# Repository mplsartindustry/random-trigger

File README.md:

# random-trigger

Eurorack trigger randomizer and white noise generator

#### Front View:

#### Back View:

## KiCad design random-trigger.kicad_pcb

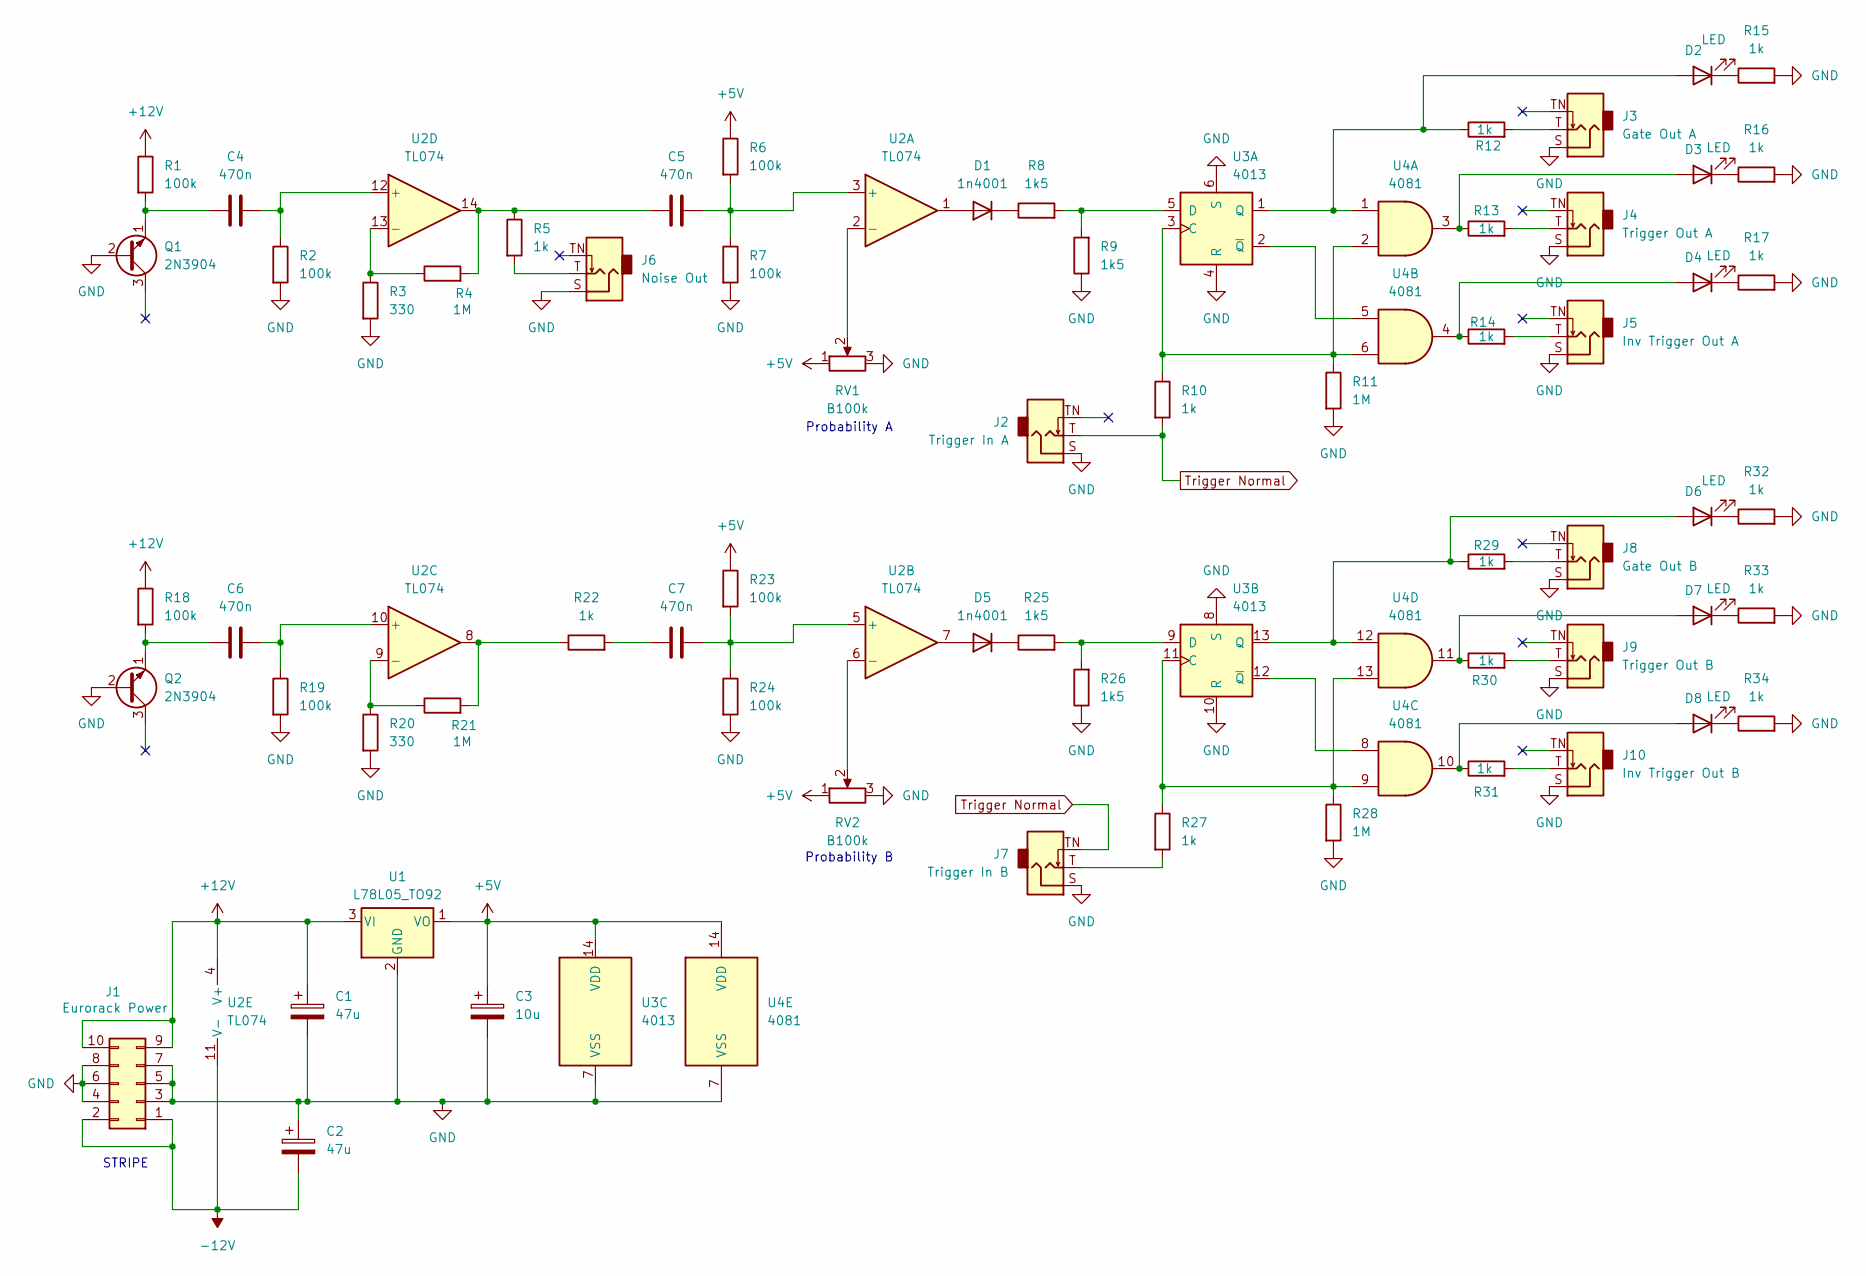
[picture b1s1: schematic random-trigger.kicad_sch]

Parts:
C1, C2: 47u; CP_Radial_D5.0mm_P2.50mm
C3: 10u; CP_Radial_D5.0mm_P2.50mm
C4, C5, C6, C7: 470n; C_Rect_L7.2mm_W3.5mm_P5.00mm_FKS2_FKP2_MKS2_MKP2
D1, D5: 1n4001; D_A-405_P7.62mm_Horizontal
D2, D3, D4, D6, D7, D8: LED; LED_D3.0mm
J1: Eurorack Power; IDC-Header_2x05_P2.54mm_Vertical
J2: Trigger In A; Jack_3.5mm_QingPu_WQP-PJ301BM_Vertical
J3: Gate Out A; Jack_3.5mm_QingPu_WQP-PJ301BM_Vertical
J4: Trigger Out A; Jack_3.5mm_QingPu_WQP-PJ301BM_Vertical
J5: Inv Trigger Out A; Jack_3.5mm_QingPu_WQP-PJ301BM_Vertical
J6: Noise Out; Jack_3.5mm_QingPu_WQP-PJ301BM_Vertical
J7: Trigger In B; Jack_3.5mm_QingPu_WQP-PJ301BM_Vertical
J8: Gate Out B; Jack_3.5mm_QingPu_WQP-PJ301BM_Vertical
J9: Trigger Out B; Jack_3.5mm_QingPu_WQP-PJ301BM_Vertical
J10: Inv Trigger Out B; Jack_3.5mm_QingPu_WQP-PJ301BM_Vertical
Q1, Q2: 2N3904; TO-92_Inline
R1, R2, R6, R7, R18, R19, R23, R24: 100k; R_Axial_DIN0207_L6.3mm_D2.5mm_P7.62mm_Horizontal
R3, R20: 330; R_Axial_DIN0207_L6.3mm_D2.5mm_P7.62mm_Horizontal
R4, R11, R21, R28: 1M; R_Axial_DIN0207_L6.3mm_D2.5mm_P7.62mm_Horizontal
R5, R10, R12, R13, R14, R15, R16, R17, R22, R27, R29, R30, R31, R32, R33, R34: 1k; R_Axial_DIN0207_L6.3mm_D2.5mm_P7.62mm_Horizontal
R8, R9, R25, R26: 1k5; R_Axial_DIN0207_L6.3mm_D2.5mm_P7.62mm_Horizontal
RV1, RV2: B100k; Potentiometer_Alpha_RD901F-40-00D_Single_Vertical
U1: L78L05_TO92; TO-92_Inline
U2: TL074; DIP-14_W7.62mm_Socket_WithChip
U3: 4013; DIP-14_W7.62mm_Socket_WithChip
U4: 4081; DIP-14_W7.62mm_Socket_WithChip

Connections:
+5V: C3.1, R6.1, R23.1, RV1.1, RV2.1, U1.1 (VO), U3.14 (VDD), U4.14 (VDD)
+12V: C1.1, J1.9, J1.10, R1.1, R18.1, U1.3 (VI), U2.4 (V+)
-12V: C2.2, J1.1, J1.2, U2.11 (V-)
GND: C1.2, C2.1, C3.2, J1.3, J1.4, J1.5, J1.6, J1.7, J1.8, J2.S, J3.S, J4.S, J5.S, J6.S, J7.S, J8.S, J9.S, J10.S, Q1.2 (B), Q2.2 (B), R2.2, R3.2, R7.2, R9.1, R11.2, R15.2, R16.2, R17.2, R19.2, R20.2, R24.2, R26.1, R28.2, R32.2, R33.2, R34.2, RV1.3, RV2.3, U1.2 (GND), U3.4 (R), U3.6 (S), U3.7 (VSS), U3.8 (S), U3.10 (R), U4.7 (VSS)
unnamed: C5.1, R4.2, R5.1, U2.14
unnamed: C7.1, R22.2
unnamed: D1.2 (A), U2.1
unnamed: D1.1 (K), R8.1
unnamed: D2.2 (A), R12.1, U3.1 (Q), U4.1
unnamed: D2.1 (K), R15.1
unnamed: D3.2 (A), R13.1, U4.3
unnamed: D3.1 (K), R16.1
unnamed: D4.2 (A), R14.1, U4.4
unnamed: D4.1 (K), R17.1
unnamed: D5.2 (A), U2.7
unnamed: D5.1 (K), R25.1
unnamed: D6.2 (A), R29.1, U3.13 (Q), U4.12
unnamed: D6.1 (K), R32.1
unnamed: D7.2 (A), R30.1, U4.11
unnamed: D7.1 (K), R33.1
unnamed: D8.2 (A), R31.1, U4.10
unnamed: D8.1 (K), R34.1
unnamed: J3.T, R12.2
unnamed: J4.T, R13.2
unnamed: J5.T, R14.2
unnamed: J6.T, R5.2
unnamed: J7.T, R27.2
unnamed: J8.T, R29.2
unnamed: J9.T, R30.2
unnamed: J10.T, R31.2
unnamed: C4.1, Q1.1 (E), R1.2
unnamed: C6.1, Q2.1 (E), R18.2
unnamed: R21.2, R22.1, U2.8
unnamed: C5.2, R6.2, R7.1, U2.3 (+)
unnamed: RV1.2, U2.2 (-)
unnamed: C7.2, R23.2, R24.1, U2.5 (+)
unnamed: RV2.2, U2.6 (-)
unnamed: C6.2, R19.1, U2.10 (+)
unnamed: R20.1, R21.1, U2.9 (-)
unnamed: C4.2, R2.1, U2.12 (+)
unnamed: R3.1, R4.1, U2.13 (-)
unnamed: R10.1, R11.1, U3.3 (C), U4.2, U4.6
unnamed: R8.2, R9.2, U3.5 (D)
unnamed: U3.2 (~Q), U4.5
unnamed: R27.1, R28.1, U3.11 (C), U4.9, U4.13
unnamed: R25.2, R26.2, U3.9 (D)
unnamed: U3.12 (~Q), U4.8
Trigger Normal: J2.T, J7.TN, R10.2

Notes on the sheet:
Probability B
STRIPE
Probability A

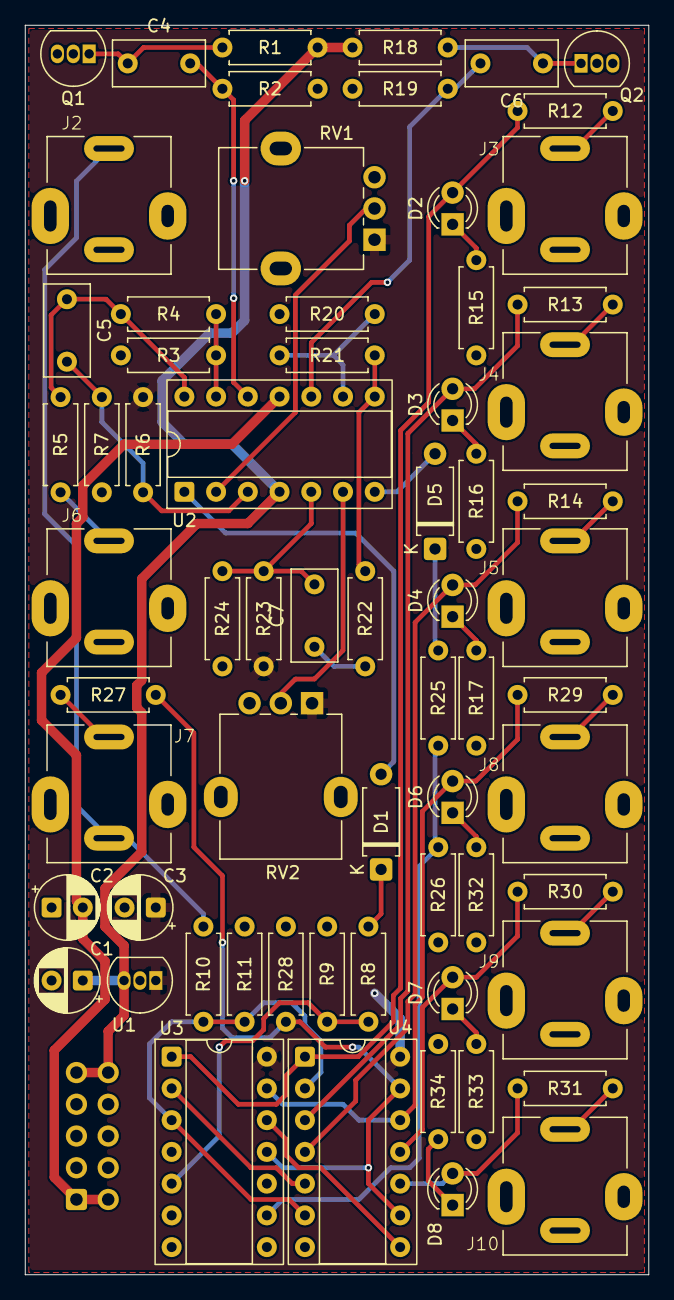
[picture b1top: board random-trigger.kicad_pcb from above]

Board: 2 copper layers, 49.9 x 100.0 mm, 67 parts (1 on the bottom side), 48 nets.

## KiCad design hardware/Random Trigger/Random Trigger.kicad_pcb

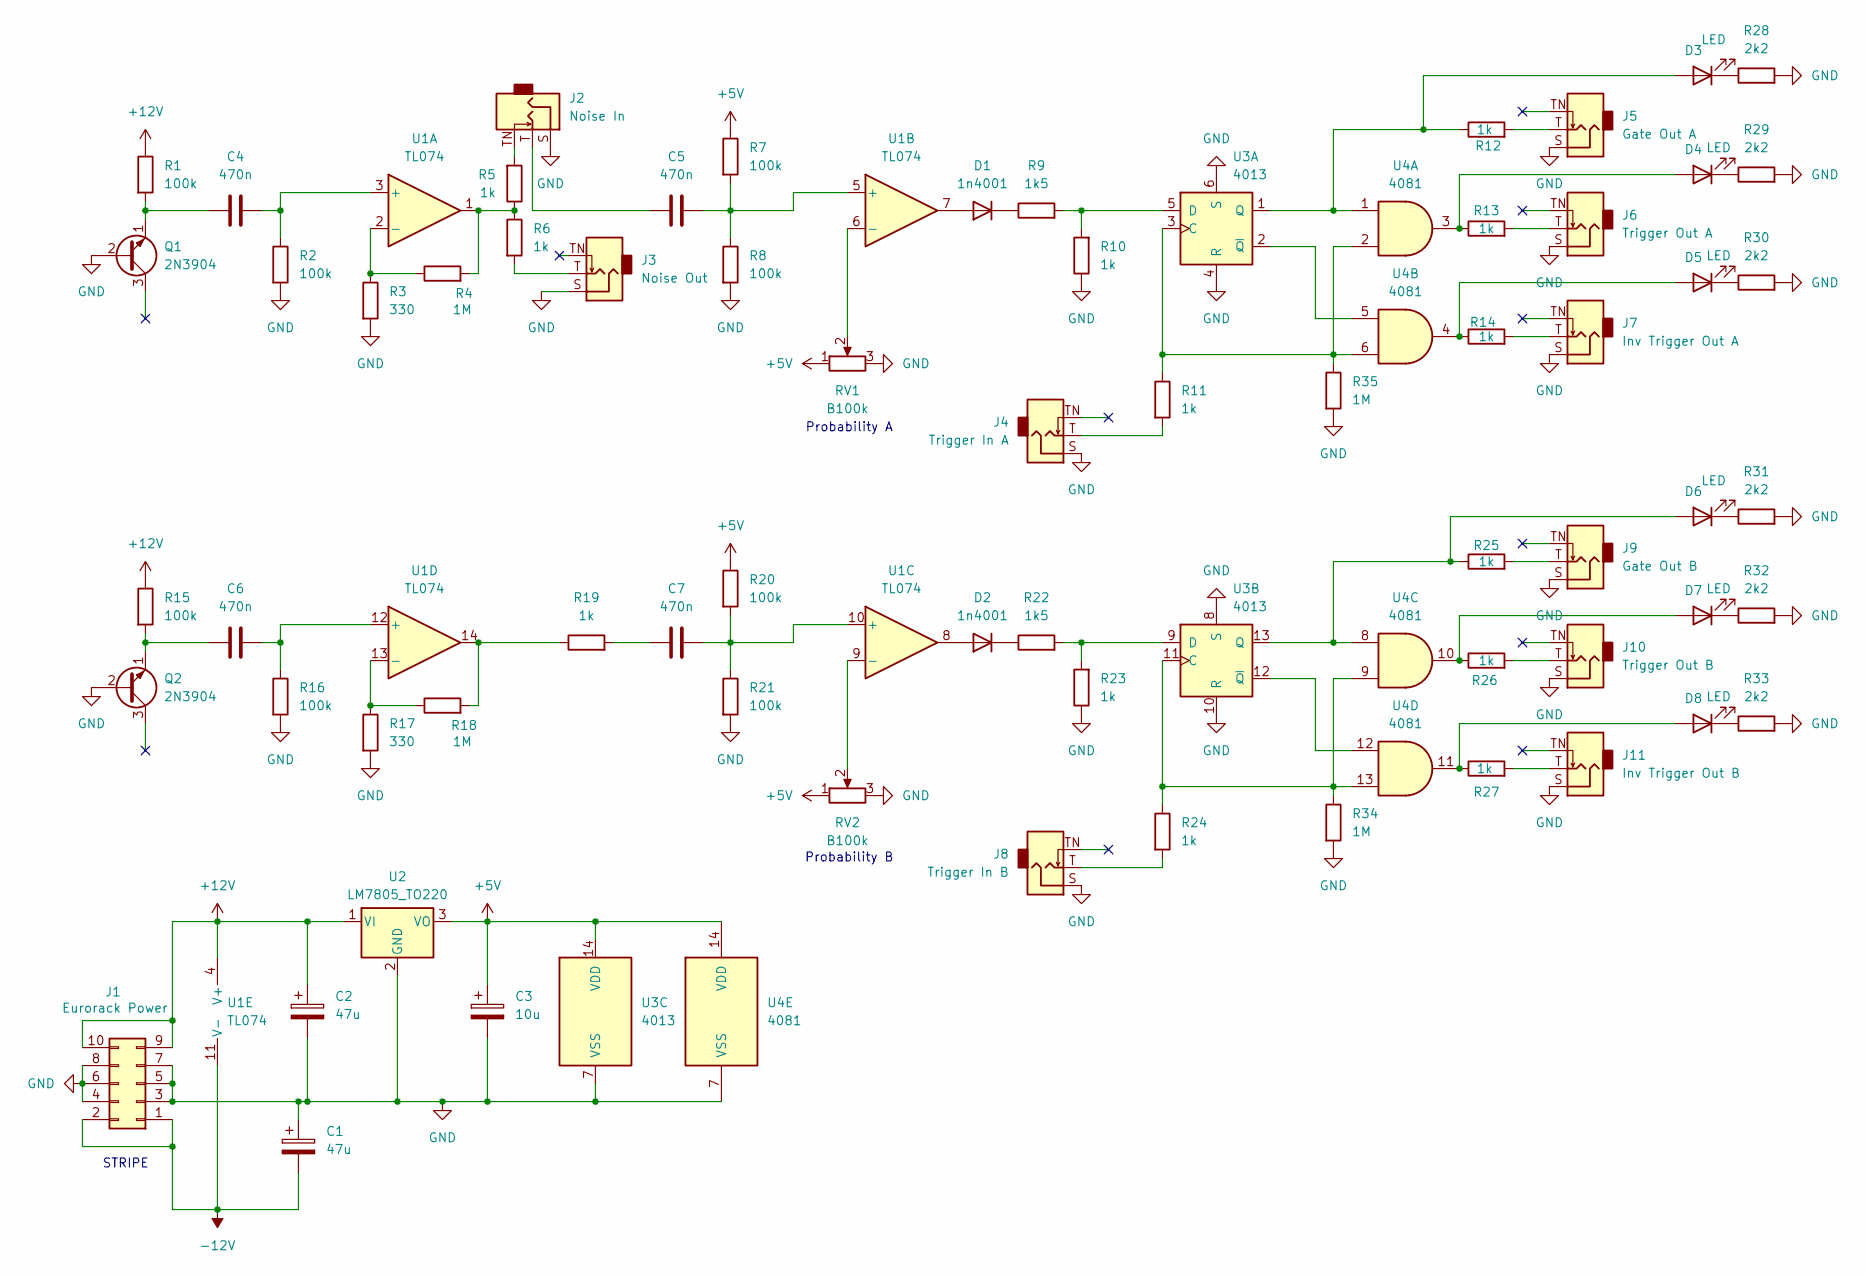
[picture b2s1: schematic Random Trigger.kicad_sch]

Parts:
C1, C2: 47u; CP_Radial_D6.3mm_P2.50mm
C3: 10u; CP_Radial_D5.0mm_P2.50mm
C4, C5, C6, C7: 470n; C_Rect_L7.0mm_W3.5mm_P5.00mm
D1, D2: 1n4001; D_A-405_P7.62mm_Horizontal
D3, D4, D5, D6, D7, D8: LED; LED_D3.0mm
J1: Eurorack Power; IDC-Header_2x05_P2.54mm_Vertical
J2: Noise In; Jack_3.5mm_QingPu_WQP-PJ301BM_Vertical
J3: Noise Out; Jack_3.5mm_QingPu_WQP-PJ301BM_Vertical
J4: Trigger In A; Jack_3.5mm_QingPu_WQP-PJ301BM_Vertical
J5: Gate Out A; Jack_3.5mm_QingPu_WQP-PJ301BM_Vertical
J6: Trigger Out A; Jack_3.5mm_QingPu_WQP-PJ301BM_Vertical
J7: Inv Trigger Out A; Jack_3.5mm_QingPu_WQP-PJ301BM_Vertical
J8: Trigger In B; Jack_3.5mm_QingPu_WQP-PJ301BM_Vertical
J9: Gate Out B; Jack_3.5mm_QingPu_WQP-PJ301BM_Vertical
J10: Trigger Out B; Jack_3.5mm_QingPu_WQP-PJ301BM_Vertical
J11: Inv Trigger Out B; Jack_3.5mm_QingPu_WQP-PJ301BM_Vertical
Q1, Q2: 2N3904; TO-92_Inline
R1, R2, R7, R8, R15, R16, R20, R21: 100k; R_Axial_DIN0207_L6.3mm_D2.5mm_P7.62mm_Horizontal
R3, R17: 330; R_Axial_DIN0207_L6.3mm_D2.5mm_P7.62mm_Horizontal
R4, R18, R34, R35: 1M; R_Axial_DIN0207_L6.3mm_D2.5mm_P7.62mm_Horizontal
R5, R6, R10, R11, R12, R13, R14, R19, R23, R24, R25, R26, R27: 1k; R_Axial_DIN0207_L6.3mm_D2.5mm_P7.62mm_Horizontal
R9, R22: 1k5; R_Axial_DIN0207_L6.3mm_D2.5mm_P7.62mm_Horizontal
R28, R29, R30, R31, R32, R33: 2k2; R_Axial_DIN0207_L6.3mm_D2.5mm_P7.62mm_Horizontal
RV1, RV2: B100k; Potentiometer_Alpha_RD901F-40-00D_Single_Vertical
U1: TL074; DIP-14_W7.62mm_Socket
U2: LM7805_TO220; TO-220-3_Vertical
U3: 4013; DIP-14_W7.62mm_Socket
U4: 4081; DIP-14_W7.62mm_Socket

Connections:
+5V: C3.1, R7.1, R20.1, RV1.1, RV2.1, U2.3 (VO), U3.14 (VDD), U4.14 (VDD)
+12V: C2.1, J1.9, J1.10, R1.1, R15.1, U1.4 (V+), U2.1 (VI)
-12V: C1.2, J1.1, J1.2, U1.11 (V-)
GND: C1.1, C2.2, C3.2, J1.3, J1.4, J1.5, J1.6, J1.7, J1.8, J2.S, J3.S, J4.S, J5.S, J6.S, J7.S, J8.S, J9.S, J10.S, J11.S, Q1.2 (B), Q2.2 (B), R2.2, R3.2, R8.2, R10.1, R16.2, R17.2, R21.2, R23.1, R28.2, R29.2, R30.2, R31.2, R32.2, R33.2, R34.2, R35.2, RV1.3, RV2.3, U2.2 (GND), U3.4 (R), U3.6 (S), U3.7 (VSS), U3.8 (S), U3.10 (R), U4.7 (VSS)
unnamed: C5.1, J2.T
unnamed: C7.1, R19.2
unnamed: D1.2 (A), U1.7
unnamed: D1.1 (K), R9.1
unnamed: D2.2 (A), U1.8
unnamed: D2.1 (K), R22.1
unnamed: D3.2 (A), R12.1, U3.1 (Q), U4.1
unnamed: D3.1 (K), R28.1
unnamed: D4.2 (A), R13.1, U4.3
unnamed: D4.1 (K), R29.1
unnamed: D5.2 (A), R14.1, U4.4
unnamed: D5.1 (K), R30.1
unnamed: D6.2 (A), R25.1, U3.13 (Q), U4.8
unnamed: D6.1 (K), R31.1
unnamed: D7.2 (A), R26.1, U4.10
unnamed: D7.1 (K), R32.1
unnamed: D8.2 (A), R27.1, U4.11
unnamed: D8.1 (K), R33.1
unnamed: J2.TN, R5.2
unnamed: J3.T, R6.2
unnamed: J4.T, R11.2
unnamed: J5.T, R12.2
unnamed: J6.T, R13.2
unnamed: J7.T, R14.2
unnamed: J8.T, R24.2
unnamed: J9.T, R25.2
unnamed: J10.T, R26.2
unnamed: J11.T, R27.2
unnamed: C4.1, Q1.1 (E), R1.2
unnamed: C6.1, Q2.1 (E), R15.2
unnamed: R4.2, R5.1, R6.1, U1.1
unnamed: R18.2, R19.1, U1.14
unnamed: C4.2, R2.1, U1.3 (+)
unnamed: R3.1, R4.1, U1.2 (-)
unnamed: C5.2, R7.2, R8.1, U1.5 (+)
unnamed: RV1.2, U1.6 (-)
unnamed: C7.2, R20.2, R21.1, U1.10 (+)
unnamed: RV2.2, U1.9 (-)
unnamed: C6.2, R16.1, U1.12 (+)
unnamed: R17.1, R18.1, U1.13 (-)
unnamed: R11.1, R35.1, U3.3 (C), U4.2, U4.6
unnamed: R9.2, R10.2, U3.5 (D)
unnamed: U3.2 (~Q), U4.5
unnamed: R24.1, R34.1, U3.11 (C), U4.9, U4.13
unnamed: R22.2, R23.2, U3.9 (D)
unnamed: U3.12 (~Q), U4.12

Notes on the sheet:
Probability B
STRIPE
Probability A

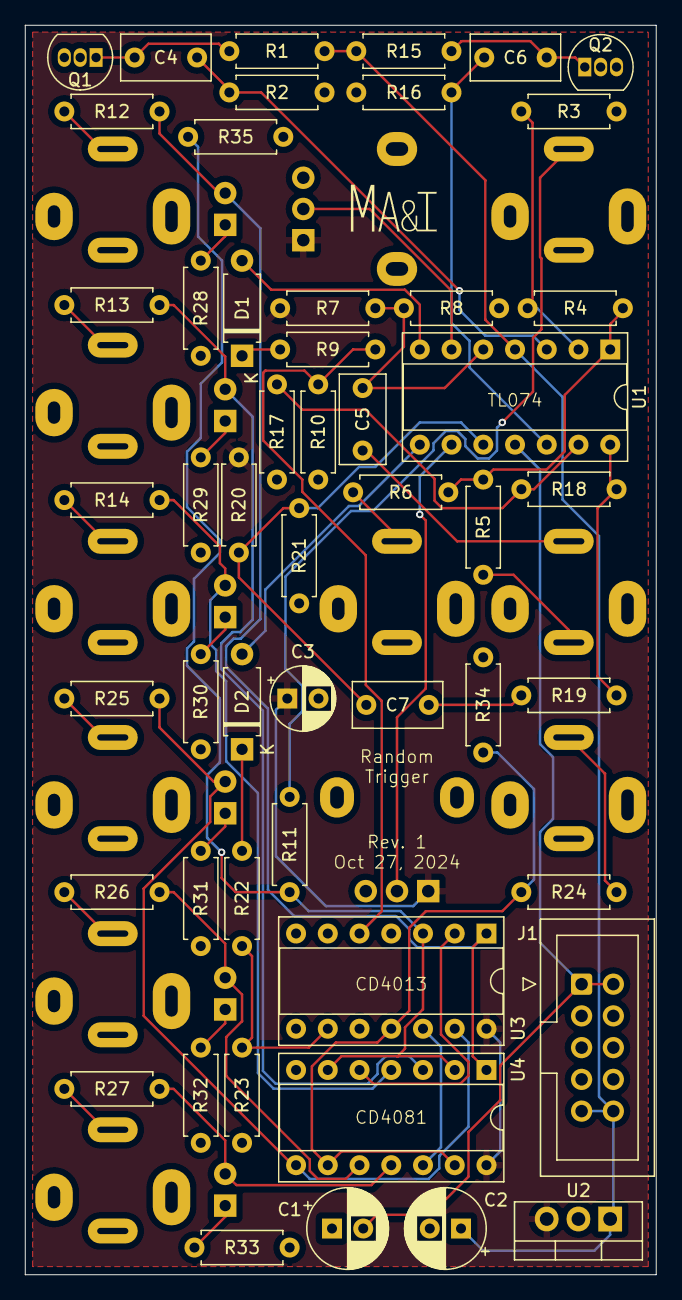
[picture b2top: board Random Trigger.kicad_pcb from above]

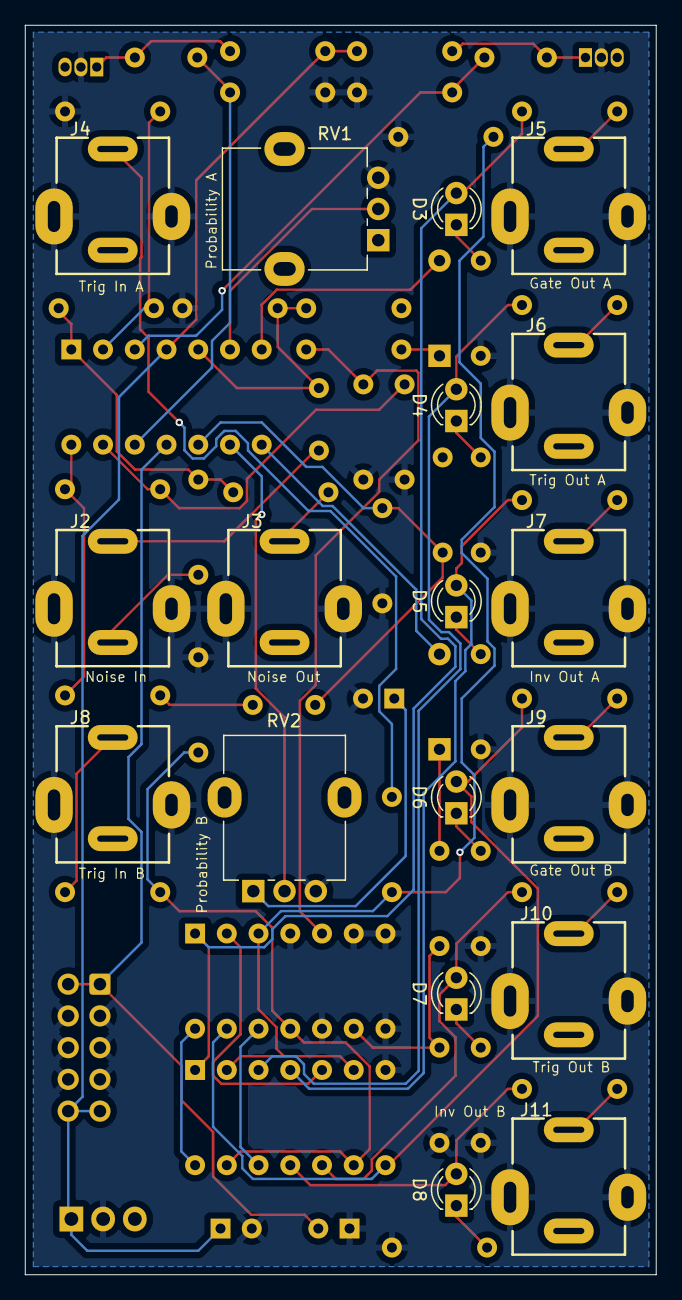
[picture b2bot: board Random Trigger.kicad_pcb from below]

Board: 2 copper layers, 50.5 x 100.0 mm, 69 parts (18 on the bottom side), 50 nets.

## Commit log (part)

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2024-11-01 Add KiCad files
2024-11-01 Add description to README
2024-11-18 Update schematic to match hardware
2026-03-23 Add trigger normalling and switch to using kicad-libraries
2026-03-25 Redo PCB to have all components on front
2026-03-25 Use correct box capacitor footprint
2026-03-25 Add square to noise out
